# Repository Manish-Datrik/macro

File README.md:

# TravelPad

travelPad is a small 4 key macropad that i have built . I wanted to create something that connects with my interest in travel, so I designed this macropad to make common travel-related tasks quicker and easier.

The idea is that instead of opening different websites manually, I can press a single key to launch things like Google Maps, flight booking sites, hotel booking websites, or my travel planner.

I designed the PCB in KiCad and created the enclosure in Fusion 360. The macropad uses a Seeed Studio XIAO RP2040 and includes a 0.91-inch OLED display.

---

## Why I Chose This Theme

I enjoy travelling and wanted my project to say. Instead of making a regular macropad, I decided to give it a travel theme with custom artwork and a layout inspired by planning trips.

The goal was to build something that is both useful and personal.

---

## Features

- 4 programmable mechanical keys
- Seeed Studio XIAO RP2040
- 0.91-inch OLED display
- USB-C connection
- Custom PCB designed in KiCad

---

## Example Shortcuts

Some example shortcuts I plan to use are:

- Open Google Maps
- Open flight booking websites
- Open hotel booking websites

## Tools Used

- KiCad 10

---

## What I Learned

While building this project I learned how to:

- Design a PCB from scratch
- Route traces and prepare Gerber files
- Add an OLED display to a custom PCB

---

## Images

I'll add screenshots of:

- Schematic
- PCB Layout
- 3D PCB View

Manish

Made for Hack Club Off Track 2026.

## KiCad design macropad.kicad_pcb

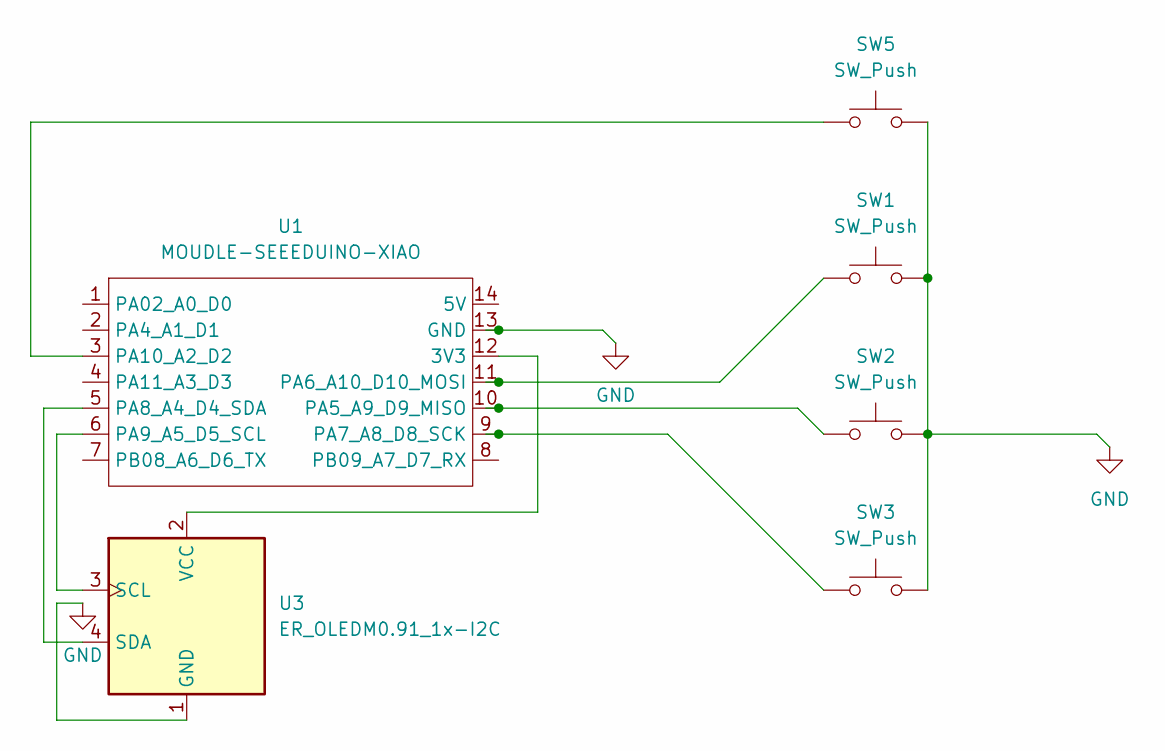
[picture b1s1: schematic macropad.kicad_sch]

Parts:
SW1, SW2, SW3, SW5: SW_Push; SW_Cherry_MX_1.00u_PCB
U1: MOUDLE-SEEEDUINO-XIAO; XIAO-Generic-Hybrid-14P-2.54-21X17.8MM
U3: ER_OLEDM0.91_1x-I2C

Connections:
GND: SW1.2, SW2.2, SW3.2, SW5.2, U1.13 (GND), U3.1 (GND)
unnamed: U1.12 (3V3), U3.2 (VCC)
unnamed: SW2.1, U1.10 (PA5_A9_D9_MISO)
unnamed: SW1.1, U1.11 (PA6_A10_D10_MOSI)
unnamed: SW3.1, U1.9 (PA7_A8_D8_SCK)
unnamed: U1.5 (PA8_A4_D4_SDA), U3.4 (SDA)
unnamed: U1.6 (PA9_A5_D5_SCL), U3.3 (SCL)
unnamed: SW5.1, U1.3 (PA10_A2_D2)

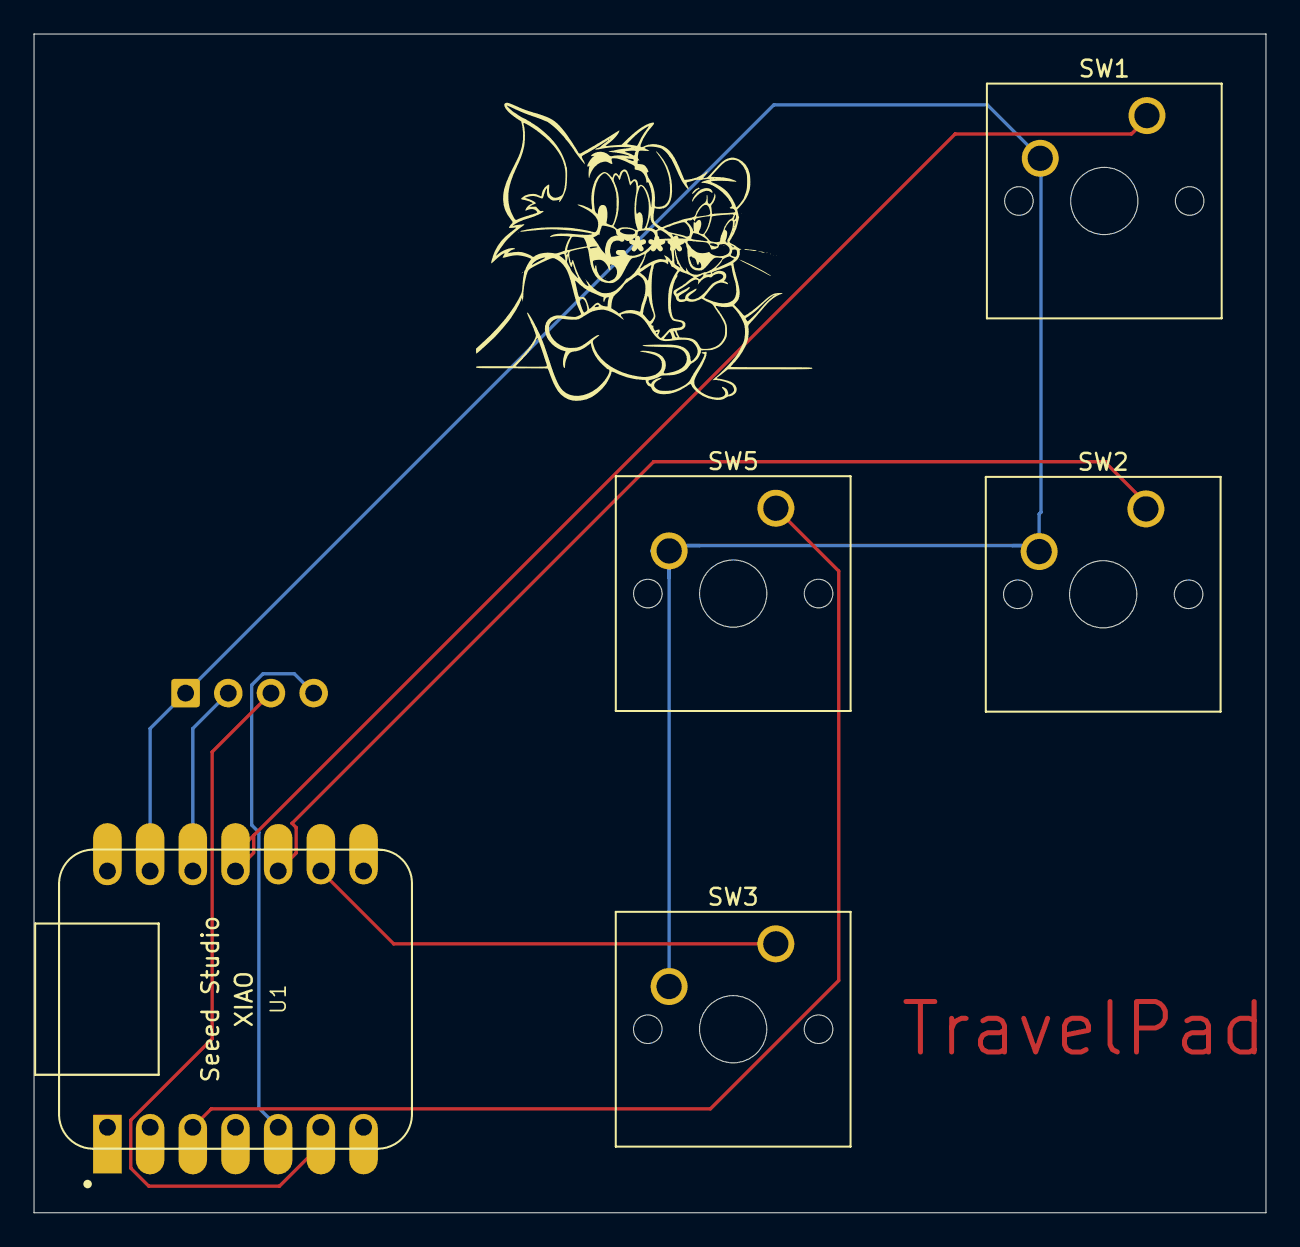
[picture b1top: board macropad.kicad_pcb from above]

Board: 2 copper layers, 73.3 x 70.1 mm, 6 parts (1 on the bottom side), 8 nets.

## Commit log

2026-06-25 first
2026-06-26 creating the top started
